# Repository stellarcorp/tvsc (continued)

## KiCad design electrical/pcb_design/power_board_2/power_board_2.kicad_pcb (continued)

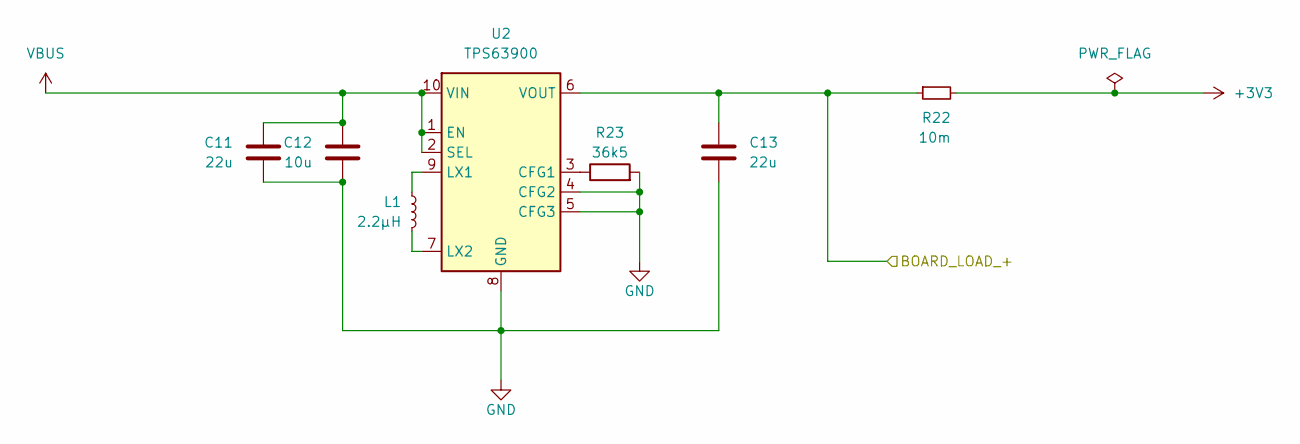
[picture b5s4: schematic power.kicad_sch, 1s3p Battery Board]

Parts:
C11, C13: 22u; Nondescript_C_0402_1005Metric
C12: 10u; Nondescript_C_0402_1005Metric
L1: 2.2µH; L_1008_2520Metric
R22: 10m; R_2512_6332Metric
R23: 36k5; Nondescript_R_0603_1608Metric
U2: TPS63900; WSON-10-1EP_2.5x2.5mm_P0.5mm_EP1.2x2mm_ThermalVias

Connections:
+3V3: R22.2; also elsewhere on the board
/Charger/BOARD_load+: C13.1, R22.1, U2.6 (VOUT); also elsewhere on the board
GND: C11.2, C12.2, C13.2, R23.2, U2.4 (CFG2), U2.5 (CFG3), U2.8 (GND), U2.11 (GND); also elsewhere on the board
unnamed: R23.1, U2.3 (CFG1)
unnamed: L1.2, U2.9 (LX1)
unnamed: L1.1, U2.7 (LX2)
VBUS: C11.1, C12.1, U2.1 (EN), U2.2 (SEL), U2.10 (VIN); also elsewhere on the board

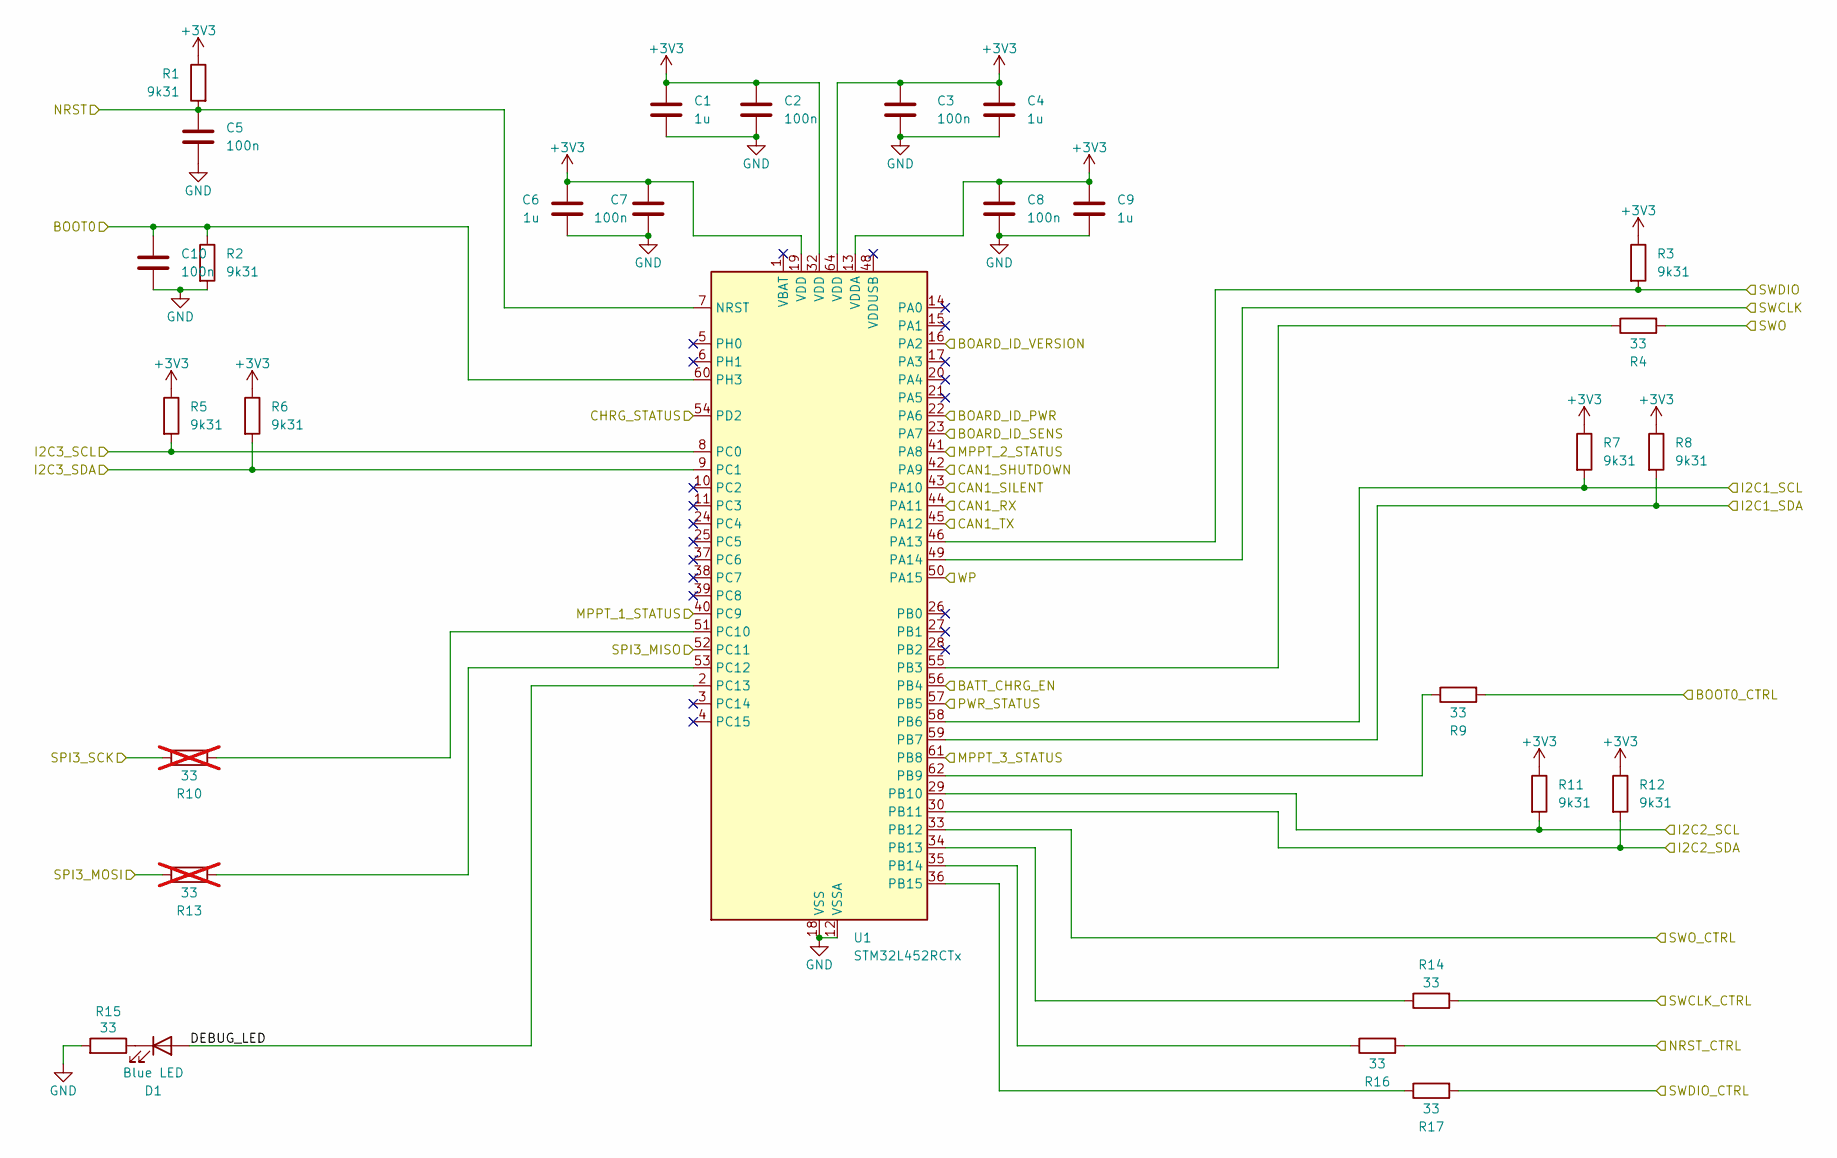
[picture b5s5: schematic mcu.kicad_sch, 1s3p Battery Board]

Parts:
C1, C4, C6, C9: 1u; Nondescript_C_0402_1005Metric
C2, C3, C5, C7, C8, C10: 100n; Nondescript_C_0402_1005Metric
D1: Blue LED; LED_0603_1608Metric
R1, R2, R3, R5, R6, R7, R8, R11, R12: 9k31; Nondescript_R_0402_1005Metric
R4, R9, R14, R15, R16, R17: 33; Nondescript_R_0402_1005Metric
R10: 33; Nondescript_R_0402_1005Metric; not fitted
R13: 33; not fitted
U1: STM32L452RCTx; LQFP-64_10x10mm_P0.5mm

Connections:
+3V3: C1.1, C2.1, C3.1, C4.1, C6.1, C7.1, C8.1, C9.1, R1.1, R3.1, R5.1, R6.1, R7.1, R8.1, R11.1, R12.1, U1.13 (VDDA), U1.19 (VDD), U1.32 (VDD), U1.64 (VDD); also elsewhere on the board
/BOOT0: C10.1, R2.1, U1.60 (PH3); also elsewhere on the board
/Board Identification/BOARD_ID_POWER: U1.22 (PA6); also elsewhere on the board
/Board Identification/BOARD_ID_SENSE: U1.23 (PA7); also elsewhere on the board
/CAN bus/CAN_RX: U1.44 (PA11); also elsewhere on the board
/CAN bus/CAN_SHUTDOWN: U1.42 (PA9); also elsewhere on the board
/CAN bus/CAN_SILENT: U1.43 (PA10); also elsewhere on the board
/CAN bus/CAN_TX: U1.45 (PA12); also elsewhere on the board
/CTRL.BOOT0: R9.2; also elsewhere on the board
/CTRL.NRST: R16.2; also elsewhere on the board
/CTRL.SWCLK: R14.2; also elsewhere on the board
/CTRL.SWDIO: R17.2; also elsewhere on the board
/CTRL.SWO: U1.33 (PB12); also elsewhere on the board
/Charger/BATT_CHRG_EN: U1.56 (PB4); also elsewhere on the board
/Charger/CHRG_STATUS: U1.54 (PD2); also elsewhere on the board
/Charger/I2C1_SDA: R8.2, U1.59 (PB7); also elsewhere on the board
/Charger/I2C1_SLC: R7.2, U1.58 (PB6); also elsewhere on the board
/Charger/I2C2_SDA: R12.2, U1.30 (PB11); also elsewhere on the board
/Charger/I2C2_SLC: R11.2, U1.29 (PB10); also elsewhere on the board
/Charger/I2C3_SDA: R6.2, U1.9 (PC1); also elsewhere on the board
/Charger/I2C3_SLC: R5.2, U1.8 (PC0); also elsewhere on the board
/Charger/MPPT_1_STATUS: U1.40 (PC9); also elsewhere on the board
/Charger/MPPT_2_STATUS: U1.41 (PA8); also elsewhere on the board
/Charger/MPPT_3_STATUS: U1.61 (PB8); also elsewhere on the board
/Charger/PWR_STATUS: U1.57 (PB5); also elsewhere on the board
/Charger/WP: U1.50 (PA15); also elsewhere on the board
/MCU/DEBUG_LED: D1.2 (A), U1.2 (PC13)
/MCU/SPI3_MISO: U1.52 (PC11)
/NRST: C5.1, R1.2, U1.7 (NRST); also elsewhere on the board
/SWCLK: U1.49 (PA14); also elsewhere on the board
/SWDIO: R3.2, U1.46 (PA13); also elsewhere on the board
/SWO: R4.2; also elsewhere on the board
GND: C1.2, C2.2, C3.2, C4.2, C5.2, C6.2, C7.2, C8.2, C9.2, C10.2, R2.2, R15.2, U1.12 (VSSA), U1.16 (PA2), U1.18 (VSS), U1.31 (VSS), U1.47 (VSS), U1.63 (VSS); also elsewhere on the board
unnamed: D1.1 (K), R15.1
unnamed: R4.1, U1.55 (PB3)
unnamed: R9.1, U1.62 (PB9)
unnamed: R14.1, U1.34 (PB13)
unnamed: R16.1, U1.35 (PB14)
unnamed: R17.1, U1.36 (PB15)
unnamed: R10.2, U1.51 (PC10)
unnamed: R13.2, U1.53 (PC12)

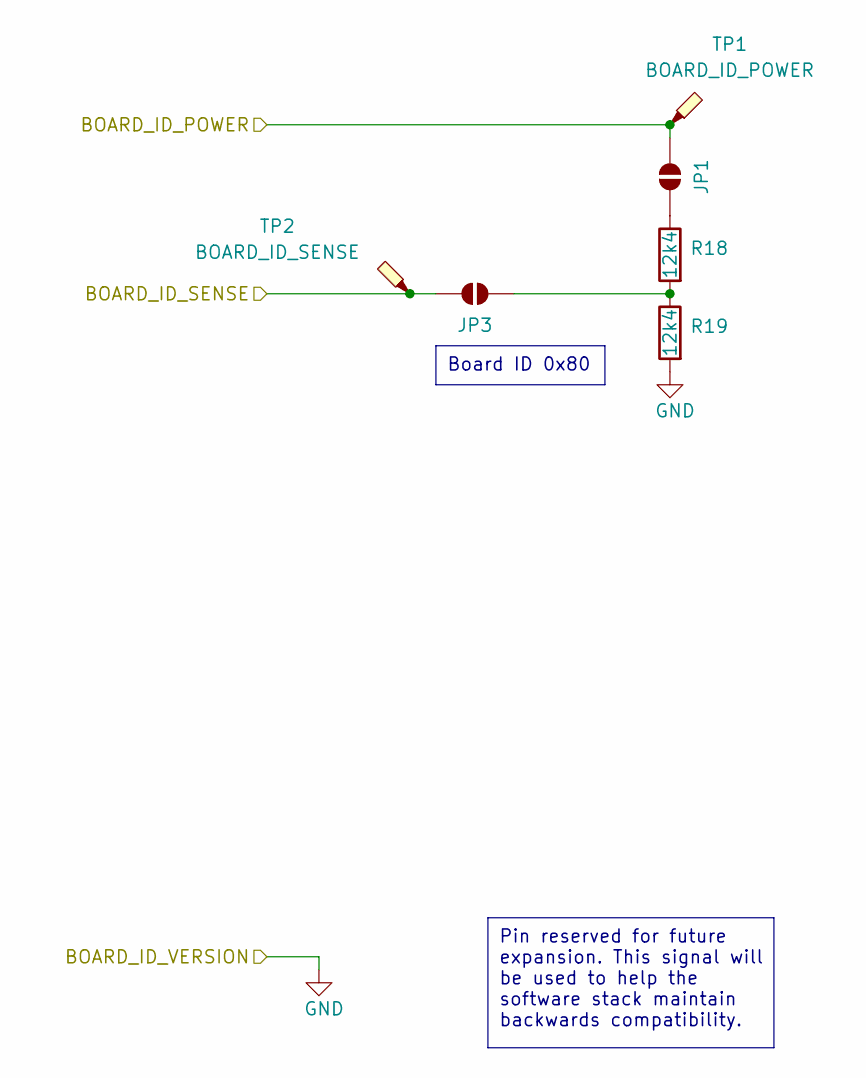
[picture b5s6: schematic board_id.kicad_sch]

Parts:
JP1, JP3: SolderJumper_2_Open; SolderJumper-2_P1.3mm_Open_RoundedPad1.0x1.5mm
R18, R19: 12k4; Nondescript_R_0402_1005Metric
TP1: BOARD_ID_POWER; TestPoint_Pad_D1.5mm
TP2: BOARD_ID_SENSE; TestPoint_Pad_D1.5mm

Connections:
/Board Identification/BOARD_ID_POWER: JP1.2 (B), TP1.1; also elsewhere on the board
/Board Identification/BOARD_ID_SENSE: JP3.1 (A), TP2.1; also elsewhere on the board
GND: R19.2; also elsewhere on the board
unnamed: JP1.1 (A), R18.1
unnamed: JP3.2 (B), R18.2, R19.1

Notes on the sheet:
Pin reserved for future expansion. This signal will be used to help the software stack maintain backwards compatibility.
Board ID 0x80

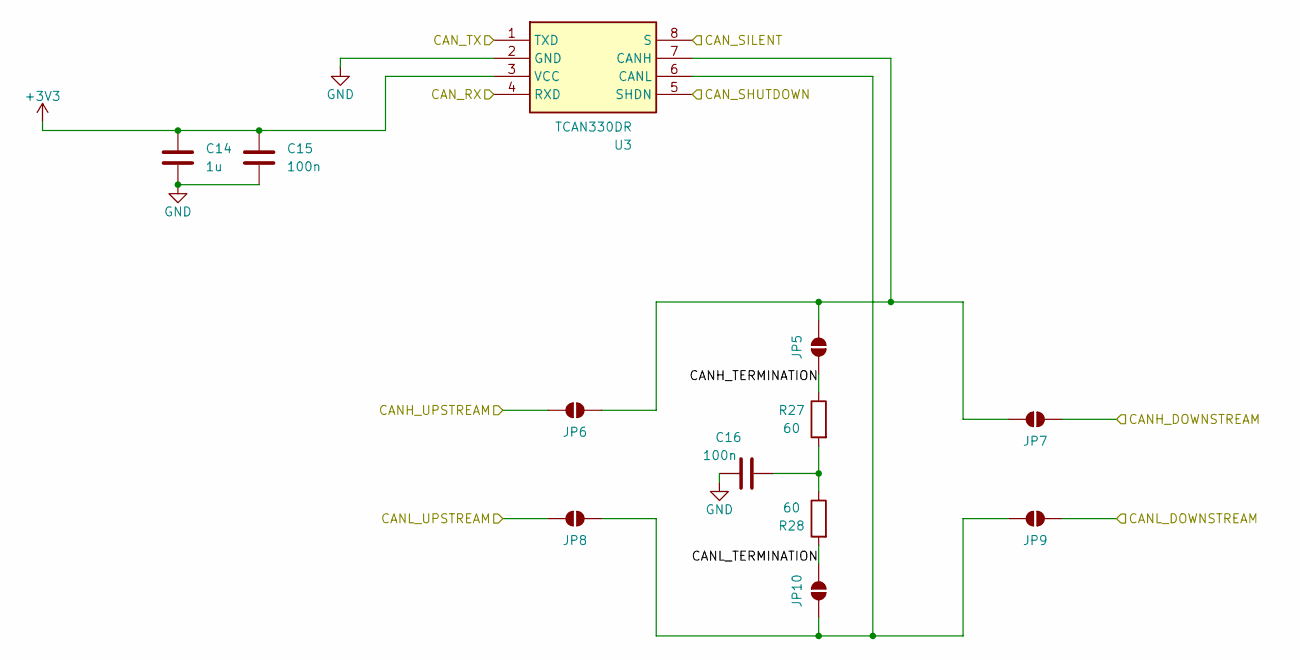
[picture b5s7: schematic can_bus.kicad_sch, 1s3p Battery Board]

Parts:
C14: 1u; Nondescript_C_0402_1005Metric
C15, C16: 100n; Nondescript_C_0402_1005Metric
JP5, JP6, JP7, JP8, JP9, JP10: SolderJumper_2_Open; SolderJumper-2_P1.3mm_Open_RoundedPad1.0x1.5mm
R27, R28: 60; Nondescript_R_0402_1005Metric
U3: TCAN330DR; SOIC127P600X175-8N; Manufacturer Part Number TCAN330DR

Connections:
+3V3: C14.1, C15.1, U3.3 (VCC); also elsewhere on the board
/CAN bus/CANH_TERMINATION: JP5.2 (B), R27.1
/CAN bus/CANL_TERMINATION: JP10.1 (A), R28.2
/CAN bus/CAN_RX: U3.4 (RXD); also elsewhere on the board
/CAN bus/CAN_SHUTDOWN: U3.5 (SHDN); also elsewhere on the board
/CAN bus/CAN_SILENT: U3.8 (S); also elsewhere on the board
/CAN bus/CAN_TX: U3.1 (TXD); also elsewhere on the board
/CANH_DOWNSTREAM: JP7.2 (B); also elsewhere on the board
/CANH_UPSTREAM: JP6.1 (A); also elsewhere on the board
/CANL_DOWNSTREAM: JP9.2 (B); also elsewhere on the board
/CANL_UPSTREAM: JP8.1 (A); also elsewhere on the board
GND: C14.2, C15.2, C16.1, U3.2 (GND); also elsewhere on the board
unnamed: C16.2, R27.2, R28.1
unnamed: JP5.1 (A), JP6.2 (B), JP7.1 (A), U3.7 (CANH)
unnamed: JP8.2 (B), JP9.1 (A), JP10.2 (B), U3.6 (CANL)

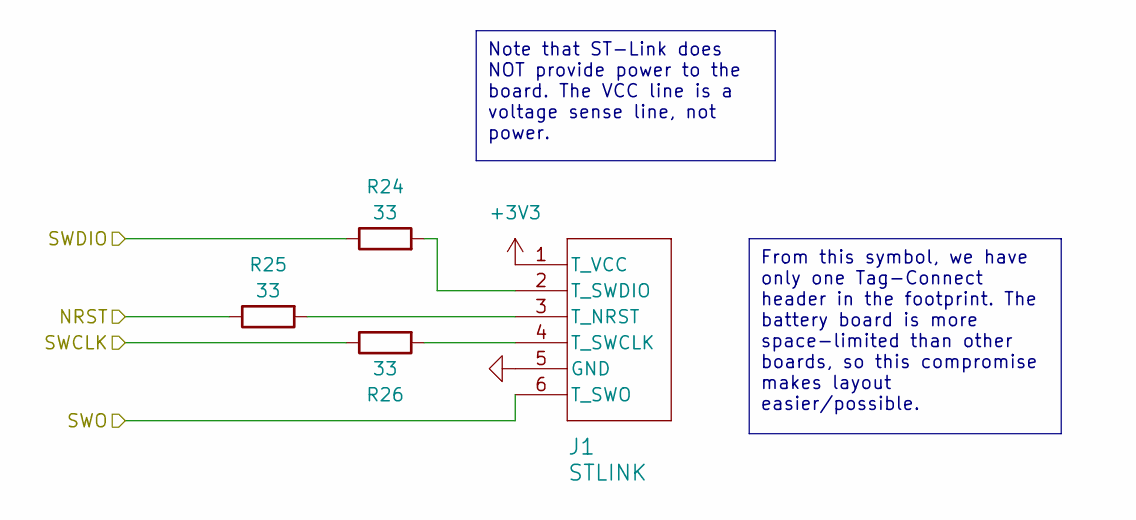
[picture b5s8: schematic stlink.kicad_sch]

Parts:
J1: STLINK; Tag-Connect_TC2030-IDC-NL_2x03_P1.27mm_Vertical
R24, R25, R26: 33; Nondescript_R_0402_1005Metric

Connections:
+3V3: J1.1 (T_VCC); also elsewhere on the board
/NRST: R25.1; also elsewhere on the board
/SWCLK: R26.1; also elsewhere on the board
/SWDIO: R24.1; also elsewhere on the board
/SWO: J1.6 (T_SWO); also elsewhere on the board
GND: J1.5 (GND); also elsewhere on the board
unnamed: J1.3 (T_NRST), R25.2
unnamed: J1.4 (T_SWCLK), R26.2
unnamed: J1.2 (T_SWDIO), R24.2

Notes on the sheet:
Note that ST-Link does NOT provide power to the board. The VCC line is a voltage sense line, not power.
From this symbol, we have only one Tag-Connect header in the footprint. The battery board is more space-limited than other boards, so this compromise makes layout easier/possible.

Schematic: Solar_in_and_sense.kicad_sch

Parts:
D2, D3, D4, D5, D6, D7, D8, D9, D10: SM74611KTTR; SM74611; PARTREV B
J5, J6: Molex_504050-0691; Manufacturer Part Number 504050-0691
R20, R21, R43, R44, R45, R46: 1; R_2512_6332Metric
R49, R50: 9k31; Nondescript_R_0402_1005Metric
U12, U13: PAC1932T-I/JQ; PAC1934

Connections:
+3V3: R49.1, R50.1, U12.2 (VDD), U12.15 (VDDI/O), U12.16 (*PWRDN), U13.2 (VDD), U13.9 (SENSE4-), U13.15 (VDDI/O), U13.16 (*PWRDN); also elsewhere on the board
/Charger/BOARD_load+: U13.10 (SENSE4+); also elsewhere on the board
/Charger/BUS_Load+: U13.11 (SENSE1+); also elsewhere on the board
/Charger/I2C2_SDA: U13.4 (SM_CLK); also elsewhere on the board
/Charger/I2C2_SLC: U13.5 (SM_DATA); also elsewhere on the board
/Charger/I2C3_SDA: U12.4 (SM_CLK); also elsewhere on the board
/Charger/I2C3_SLC: U12.5 (SM_DATA); also elsewhere on the board
/Charger/Solar and Sense/MPPT_1/VOUT: D4.1 (ANODE_1), D4.3 (ANODE_3); also elsewhere on the board
/Charger/Solar and Sense/MPPT_2/VOUT: D7.1 (ANODE_1), D7.3 (ANODE_3); also elsewhere on the board
/Charger/Solar and Sense/MPPT_3/VOUT: D10.1 (ANODE_1), D10.3 (ANODE_3); also elsewhere on the board
/Charger/Solar and Sense/MPPT_OUT: D4.4 (CATHODE), D7.4 (CATHODE), D10.4 (CATHODE); also elsewhere on the board
/Charger/Solar and Sense/SSx1: R21.2, U13.7 (SENSE3-); also elsewhere on the board
/Charger/Solar and Sense/SSx2: D3.1 (ANODE_1), D3.3 (ANODE_3), R20.1, U13.14 (SENSE2-)
/Charger/Solar and Sense/SSy1: R44.2, U12.12 (SENSE1-); also elsewhere on the board
/Charger/Solar and Sense/SSy2: D6.1 (ANODE_1), D6.3 (ANODE_3), R43.1, U12.14 (SENSE2-)
/Charger/Solar and Sense/SSz1: R46.2, U12.7 (SENSE3-); also elsewhere on the board
/Charger/Solar and Sense/SSz2: D9.1 (ANODE_1), D9.3 (ANODE_3), R45.1, U12.9 (SENSE4-)
/Charger/Solar and Sense/Solar_x1+: D3.4 (CATHODE), J5.1, R21.1, U13.8 (SENSE3+)
/Charger/Solar and Sense/Solar_x2+: D2.4 (CATHODE), J5.2, J6.1, R20.2, U13.13 (SENSE2+)
/Charger/Solar and Sense/Solar_y1+: D6.4 (CATHODE), J5.3, R44.1, U12.11 (SENSE1+)
/Charger/Solar and Sense/Solar_y2+: D5.4 (CATHODE), J5.4, J6.3, R43.2, U12.13 (SENSE2+)
/Charger/Solar and Sense/Solar_z1+: D9.4 (CATHODE), J5.5, R46.1, U12.8 (SENSE3+)
/Charger/Solar and Sense/Solar_z2+: D8.4 (CATHODE), J5.6, J6.5, R45.2, U12.10 (SENSE4+)
GND: D2.1 (ANODE_1), D2.3 (ANODE_3), D5.1 (ANODE_1), D5.3 (ANODE_3), D8.1 (ANODE_1), D8.3 (ANODE_3), J5.7 (MP1), J5.8 (MP2), J6.2, J6.4, J6.6, J6.7 (MP1), J6.8 (MP2), U12.3 (GND), U12.6 (ADDRSEL), U13.3 (GND), U13.6 (ADDRSEL); also elsewhere on the board
unnamed: R49.2, U12.1 (SLOW/*ALERT)
unnamed: R50.2, U13.1 (SLOW/*ALERT)
VBUS: U13.12 (SENSE1-); also elsewhere on the board

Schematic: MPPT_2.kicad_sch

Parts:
C26, C27: 22n; Nondescript_C_0402_1005Metric
C28: 47u; Nondescript_C_0402_1005Metric
C29: 1u; Nondescript_C_0402_1005Metric
C30: 4.7u; Nondescript_C_0402_1005Metric
C31: 10p; Nondescript_C_0402_1005Metric
L3: 6.8u; LQH44PN_PR_MUR
R35: 4M; Nondescript_R_0402_1005Metric
R36: 200k; Nondescript_R_0402_1005Metric
R37: 100k; Nondescript_R_0402_1005Metric
R38: 1M; Nondescript_R_0402_1005Metric
U8: LTC3130EUDC-PBF; LTC3130
U9: AD5242BRUZ1M; AD5242

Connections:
+3V3: U9.5 (VDD), U9.6 (SHDN*); also elsewhere on the board
/Charger/I2C1_SDA: U9.8 (SDA); also elsewhere on the board
/Charger/I2C1_SLC: U9.7 (SCL); also elsewhere on the board
/Charger/MPPT_2_STATUS: U8.13 (PGOOD); also elsewhere on the board
/Charger/Solar and Sense/MPPT_2/CHRG_CTRL_2: R35.2, R36.2, R38.1, U8.9 (VS2/FB)
/Charger/Solar and Sense/MPPT_2/MPPT_2_DP_W: R37.1, U8.6 (MPPC), U9.3 (W1)
/Charger/Solar and Sense/MPPT_2/VOUT: C31.1, R35.1, U8.12 (EXTVCC), U8.14 (VOUT); also elsewhere on the board
/Charger/Solar and Sense/SSy1: C28.1, C29.1, U8.2 (PVIN), U8.3 (VIN), U8.4 (RUN), U9.2 (A1); also elsewhere on the board
GND: C28.2, C29.2, C30.2, R37.2, R38.2, U8.7 (GND), U8.8 (GND), U8.11 (MODE), U8.18 (PGND), U8.19 (PGND), U9.4 (B1), U9.9 (AD0), U9.10 (AD1), U9.11 (DGND), U9.12 (VSS); also elsewhere on the board
unnamed: C31.2, R36.1
unnamed: C26.1, U8.1 (BST1)
unnamed: C27.1, U8.16 (BST2)
unnamed: C26.2, L3.1, U8.20 (SW1)
unnamed: C27.2, L3.2, U8.15 (SW2)
unnamed: C30.1, U8.5 (VCC), U8.10 (VS1/ILIM)

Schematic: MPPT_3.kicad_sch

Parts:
C32, C33: 22n; Nondescript_C_0402_1005Metric
C34: 47u; Nondescript_C_0402_1005Metric
C35: 1u; Nondescript_C_0402_1005Metric
C36: 4.7u; Nondescript_C_0402_1005Metric
C37: 10p; Nondescript_C_0402_1005Metric
L4: 6.8u; LQH44PN_PR_MUR
R39: 4M; Nondescript_R_0402_1005Metric
R40: 200k; Nondescript_R_0402_1005Metric
R41: 100k; Nondescript_R_0402_1005Metric
R42: 1M; Nondescript_R_0402_1005Metric
U10: LTC3130EUDC-PBF; LTC3130
U11: AD5242BRUZ1M; AD5242

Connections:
+3V3: U11.5 (VDD), U11.6 (SHDN*); also elsewhere on the board
/Charger/I2C3_SDA: U11.8 (SDA); also elsewhere on the board
/Charger/I2C3_SLC: U11.7 (SCL); also elsewhere on the board
/Charger/MPPT_3_STATUS: U10.13 (PGOOD); also elsewhere on the board
/Charger/Solar and Sense/MPPT_3/CHRG_CTRL_3: R39.2, R40.2, R42.1, U10.9 (VS2/FB)
/Charger/Solar and Sense/MPPT_3/MPPT_3_DP_W: R41.1, U10.6 (MPPC), U11.3 (W1)
/Charger/Solar and Sense/MPPT_3/VOUT: C37.1, R39.1, U10.12 (EXTVCC), U10.14 (VOUT); also elsewhere on the board
/Charger/Solar and Sense/SSz1: C34.1, C35.1, U10.2 (PVIN), U10.3 (VIN), U10.4 (RUN), U11.2 (A1); also elsewhere on the board
GND: C34.2, C35.2, C36.2, R41.2, R42.2, U10.7 (GND), U10.8 (GND), U10.11 (MODE), U10.18 (PGND), U10.19 (PGND), U11.4 (B1), U11.9 (AD0), U11.10 (AD1), U11.11 (DGND), U11.12 (VSS); also elsewhere on the board
unnamed: C37.2, R40.1
unnamed: C32.1, U10.1 (BST1)
unnamed: C33.1, U10.16 (BST2)
unnamed: C32.2, L4.1, U10.20 (SW1)
unnamed: C33.2, L4.2, U10.15 (SW2)
unnamed: C36.1, U10.5 (VCC), U10.10 (VS1/ILIM)

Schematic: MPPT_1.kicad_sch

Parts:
C20, C21: 22n; Nondescript_C_0402_1005Metric
C22: 47u; Nondescript_C_0402_1005Metric
C23: 1u; Nondescript_C_0402_1005Metric
C24: 4.7u; Nondescript_C_0402_1005Metric
C25: 10p; Nondescript_C_0402_1005Metric
L2: 6.8u; LQH44PN_PR_MUR
R31: 4M; Nondescript_R_0402_1005Metric
R32: 200k; Nondescript_R_0402_1005Metric
R33: 100k; Nondescript_R_0402_1005Metric
R34: 1M; Nondescript_R_0402_1005Metric
U6: LTC3130EUDC-PBF; LTC3130
U7: AD5242BRUZ1M; AD5242

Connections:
+3V3: U7.5 (VDD), U7.6 (SHDN*); also elsewhere on the board
/Charger/I2C2_SDA: U7.8 (SDA); also elsewhere on the board
/Charger/I2C2_SLC: U7.7 (SCL); also elsewhere on the board
/Charger/MPPT_1_STATUS: U6.13 (PGOOD); also elsewhere on the board
/Charger/Solar and Sense/MPPT_1/CHRG_CTRL_1: R31.2, R32.2, R34.1, U6.9 (VS2/FB)
/Charger/Solar and Sense/MPPT_1/MPPT_1_DP_W: R33.1, U6.6 (MPPC), U7.3 (W1)
/Charger/Solar and Sense/MPPT_1/VOUT: C25.1, R31.1, U6.12 (EXTVCC), U6.14 (VOUT); also elsewhere on the board
/Charger/Solar and Sense/SSx1: C22.1, C23.1, U6.2 (PVIN), U6.3 (VIN), U6.4 (RUN), U7.2 (A1); also elsewhere on the board
GND: C22.2, C23.2, C24.2, R33.2, R34.2, U6.7 (GND), U6.8 (GND), U6.11 (MODE), U6.18 (PGND), U6.19 (PGND), U7.4 (B1), U7.9 (AD0), U7.10 (AD1), U7.11 (DGND), U7.12 (VSS); also elsewhere on the board
unnamed: C25.2, R32.1
unnamed: C20.1, U6.1 (BST1)
unnamed: C21.1, U6.16 (BST2)
unnamed: C20.2, L2.1, U6.20 (SW1)
unnamed: C21.2, L2.2, U6.15 (SW2)
unnamed: C24.1, U6.5 (VCC), U6.10 (VS1/ILIM)

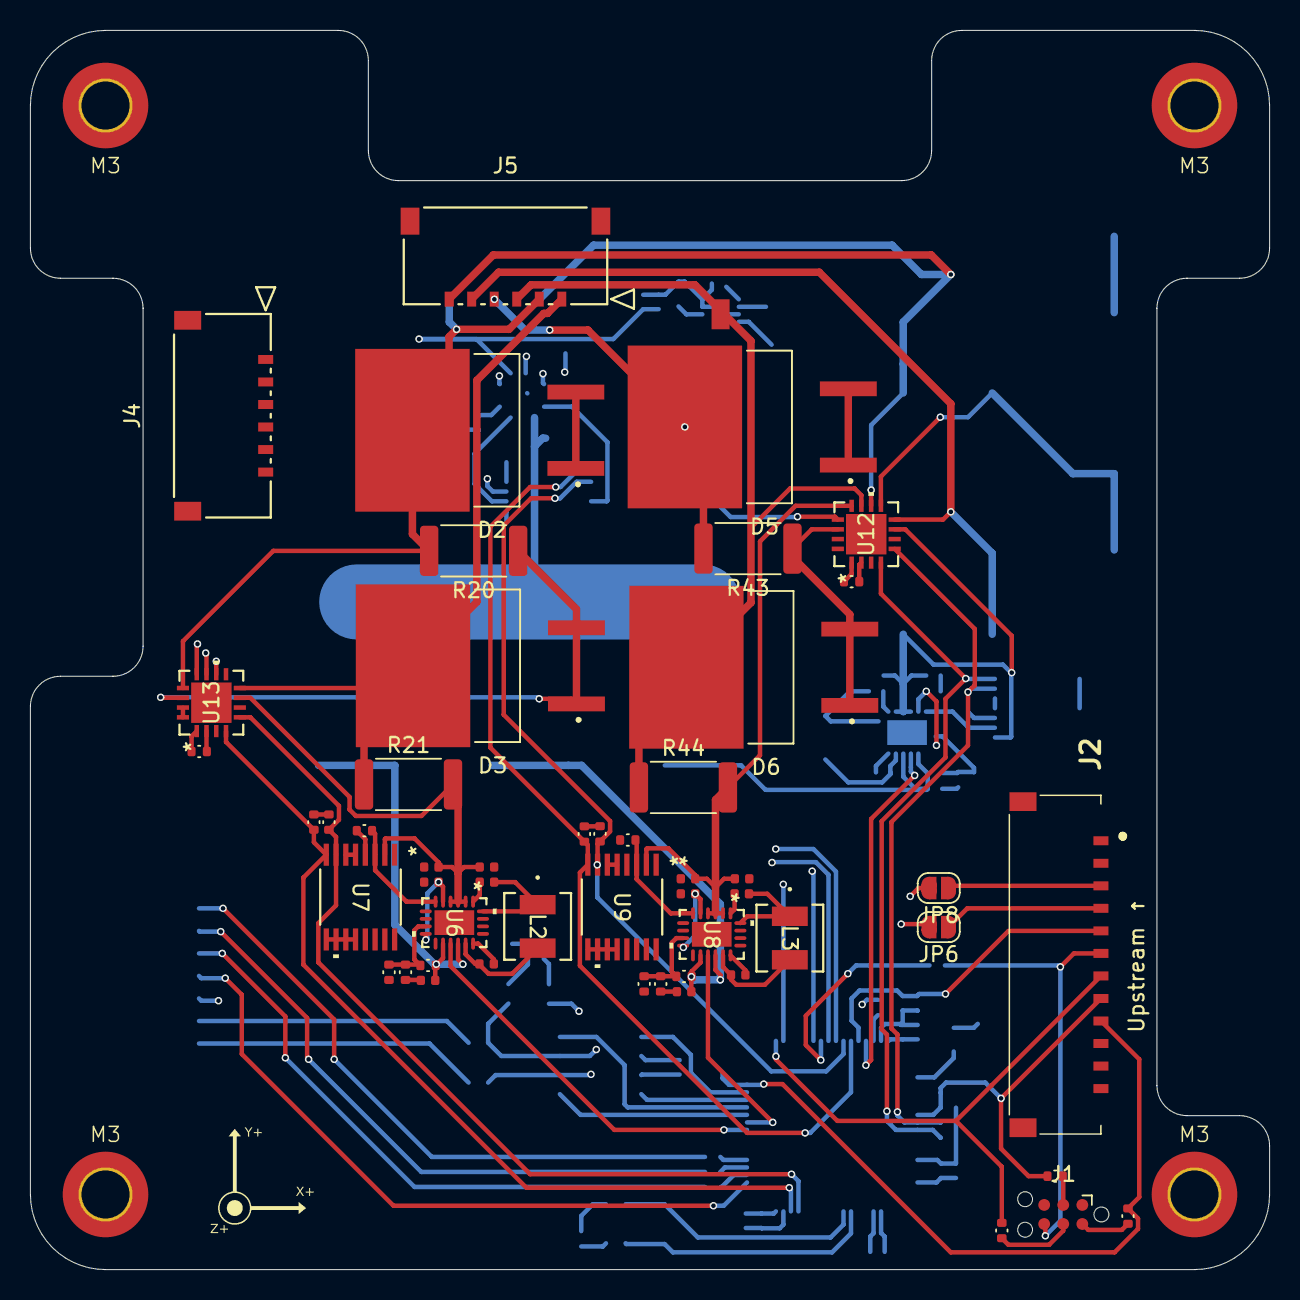
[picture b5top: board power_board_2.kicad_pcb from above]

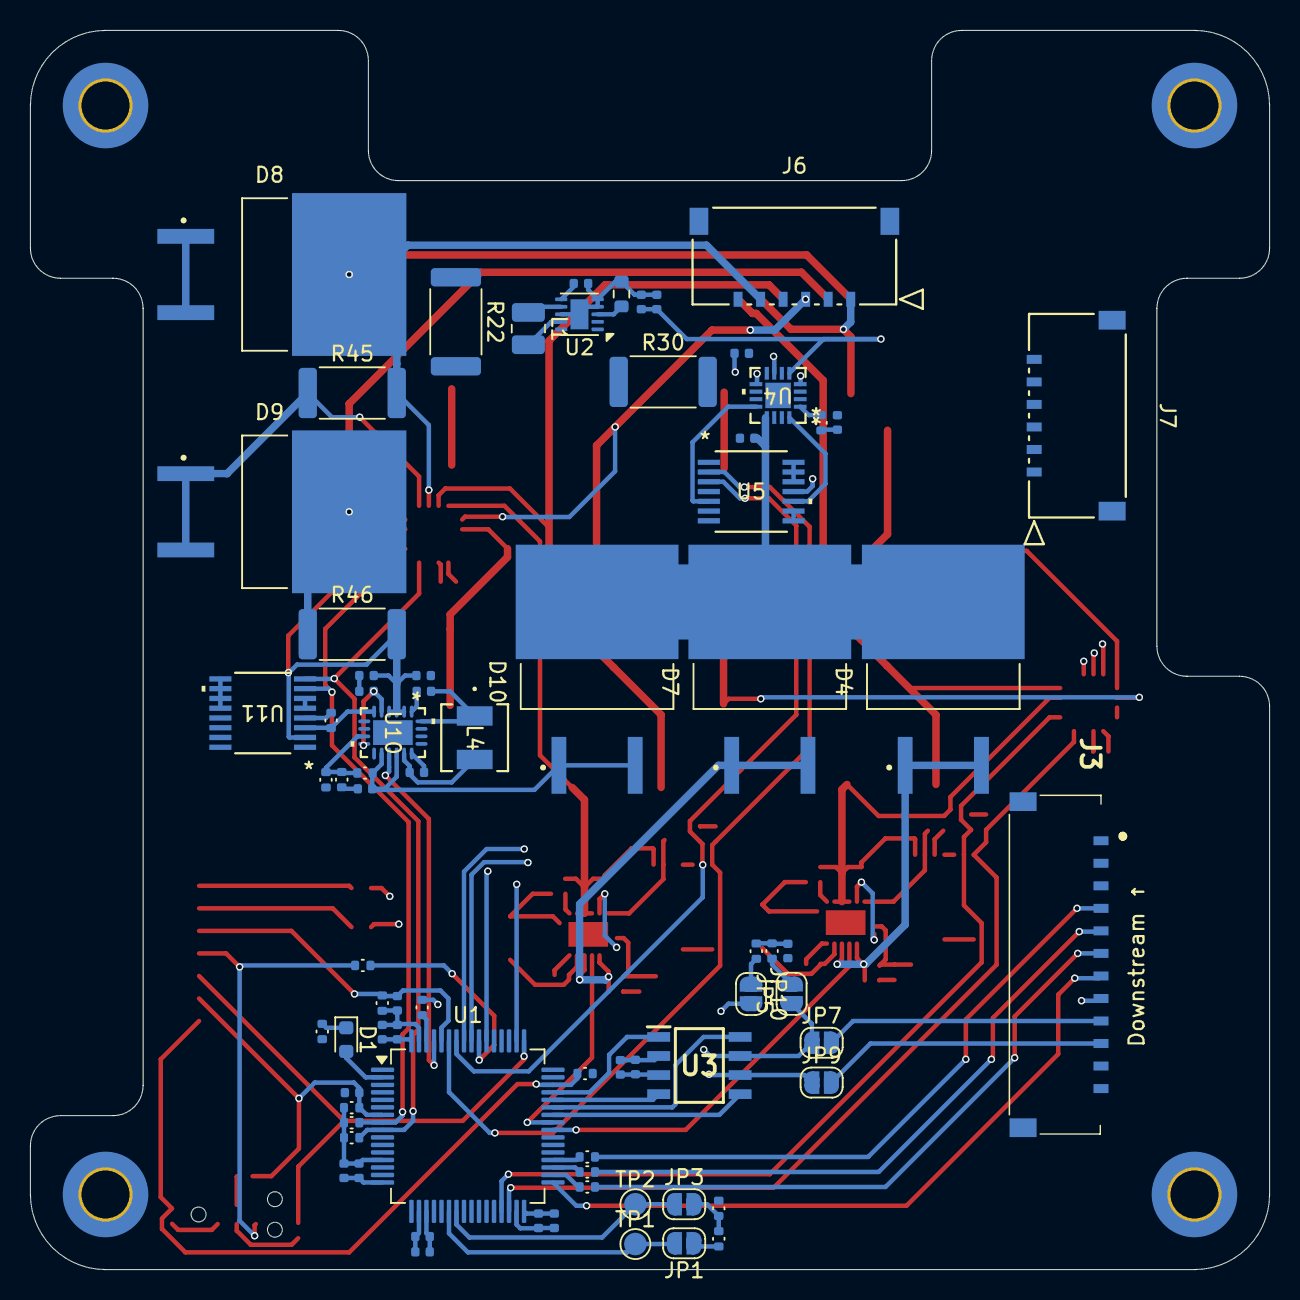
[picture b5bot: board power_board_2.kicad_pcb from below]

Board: 4 copper layers, 82.5 x 82.5 mm, 128 parts (76 on the bottom side), 104 nets.

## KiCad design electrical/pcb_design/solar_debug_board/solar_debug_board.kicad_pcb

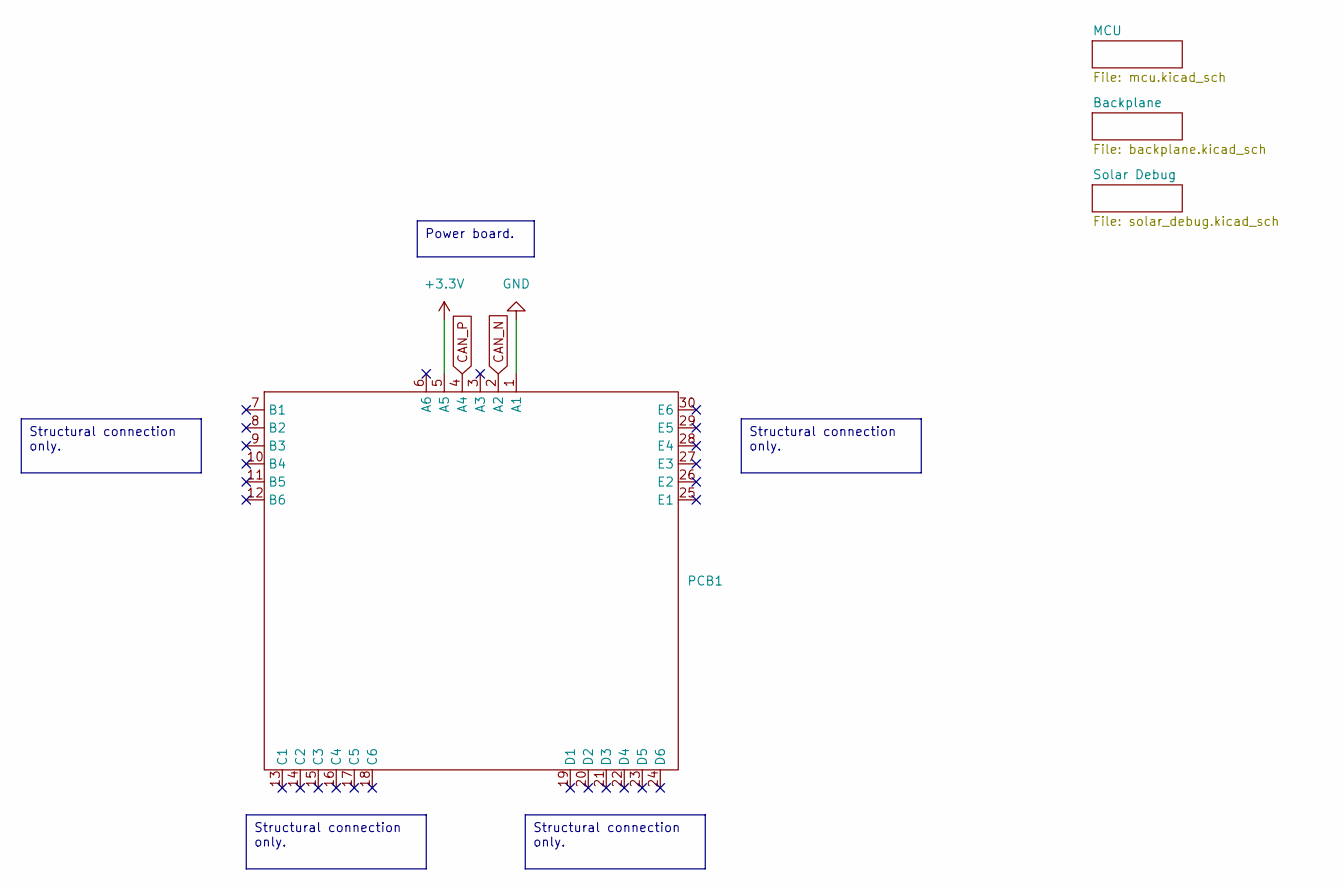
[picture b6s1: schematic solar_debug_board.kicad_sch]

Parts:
PCB1: Core_Board_PCB_Shape

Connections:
+3.3V: PCB1.5 (A5); also elsewhere on the board
CAN_N: PCB1.2 (A2); also elsewhere on the board
CAN_P: PCB1.4 (A4); also elsewhere on the board
GND: PCB1.1 (A1); also elsewhere on the board

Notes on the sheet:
Structural connection only.
Power board.

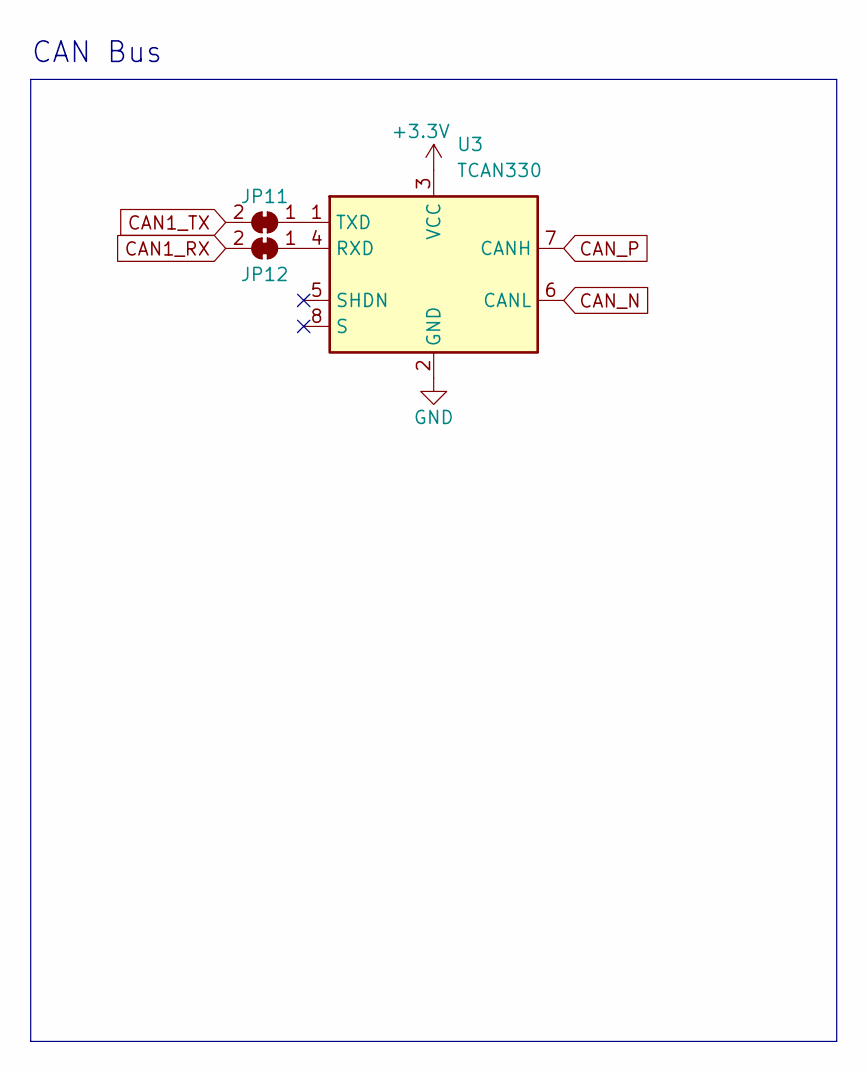
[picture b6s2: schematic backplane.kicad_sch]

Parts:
JP11, JP12: SolderJumper_2_Bridged; SolderJumper-2_P1.3mm_Bridged_RoundedPad1.0x1.5mm
U3: TCAN330; SOT-23-8; Manufacturer Part Number TCAN330DCNR

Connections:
+3.3V: U3.3 (VCC); also elsewhere on the board
CAN1_RX: JP12.2 (B); also elsewhere on the board
CAN1_TX: JP11.2 (B); also elsewhere on the board
CAN_N: U3.6 (CANL); also elsewhere on the board
CAN_P: U3.7 (CANH); also elsewhere on the board
GND: U3.2 (GND); also elsewhere on the board
unnamed: JP11.1 (A), U3.1 (TXD)
unnamed: JP12.1 (A), U3.4 (RXD)

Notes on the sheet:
CAN Bus

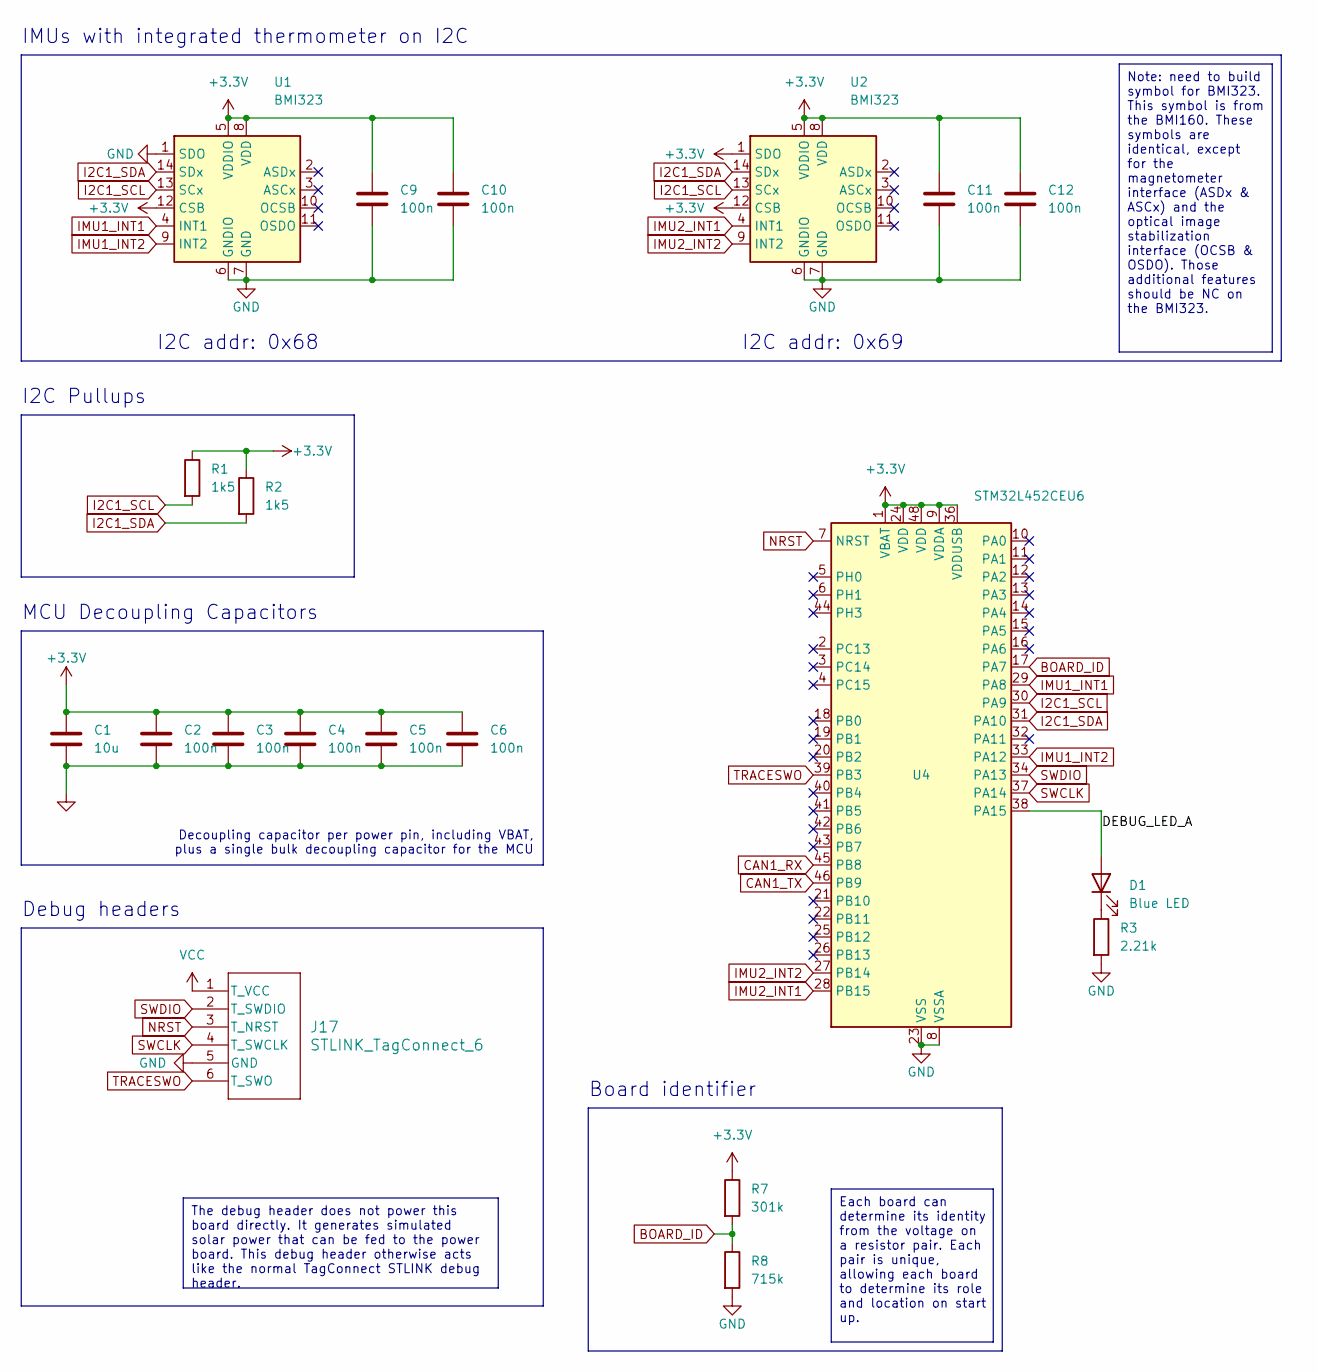
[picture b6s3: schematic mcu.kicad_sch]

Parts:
C1: 10u; C_0603_1608Metric; MPN C344022
C2, C3, C4, C5, C6: 100n; Nondescript_C_0402_1005Metric; MPN C2649549
C9, C10, C11, C12: 100n; Nondescript_C_0402_1005Metric; Manufacturer Part Number GCM155R71H104KE02J
D1: Blue LED; LED_0603_1608Metric; MPN C72041
J17: STLINK_TagConnect_6; Tag-Connect_TC2030-IDC-NL_2x03_P1.27mm_Vertical
R1, R2: 1k5; R_0402_1005Metric; MPN C25867
R3: 2.21k; Nondescript_R_0402_1005Metric; MPN C305298
R7: 301k; Nondescript_R_0402_1005Metric; MPN C25775
R8: 715k; Nondescript_R_0402_1005Metric; MPN C270585
U1, U2: BMI323; Bosch_LGA-14_3x2.5mm_P0.5mm; MPN C5368700
U4: STM32L452CEU6; QFN-48-1EP_7x7mm_P0.5mm_EP5.6x5.6mm_ThermalVias; MPN C222355

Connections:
+3.3V: C1.1, C2.1, C3.1, C4.1, C5.1, C6.1, C9.1, C10.1, C11.1, C12.1, R1.1, R2.1, R7.1, U1.5 (VDDIO), U1.8 (VDD), U1.12 (CSB), U2.1 (SDO), U2.5 (VDDIO), U2.8 (VDD), U2.12 (CSB), U4.1 (VBAT), U4.9 (VDDA), U4.24 (VDD), U4.36 (VDDUSB), U4.48 (VDD); also elsewhere on the board
/MCU/DEBUG_LED_A: D1.2 (A), U4.38 (PA15)
BOARD_ID: R7.2, R8.1, U4.17 (PA7)
CAN1_RX: U4.45 (PB8); also elsewhere on the board
CAN1_TX: U4.46 (PB9); also elsewhere on the board
GND: C1.2, C2.2, C3.2, C4.2, C5.2, C6.2, C9.2, C10.2, C11.2, C12.2, J17.5 (GND), R3.2, R8.2, U1.1 (SDO), U1.6 (GNDIO), U1.7 (GND), U2.6 (GNDIO), U2.7 (GND), U4.8 (VSSA), U4.23 (VSS), U4.35 (VSS), U4.47 (VSS), U4.49 (VSS); also elsewhere on the board
I2C1_SCL: R1.2, U1.13 (SCx), U2.13 (SCx), U4.30 (PA9)
I2C1_SDA: R2.2, U1.14 (SDx), U2.14 (SDx), U4.31 (PA10)
IMU1_INT1: U1.4 (INT1), U4.29 (PA8)
IMU1_INT2: U1.9 (INT2), U4.33 (PA12)
IMU2_INT1: U2.4 (INT1), U4.28 (PB15)
IMU2_INT2: U2.9 (INT2), U4.27 (PB14)
NRST: J17.3 (T_NRST), U4.7 (NRST)
unnamed: D1.1 (K), R3.1
SWCLK: J17.4 (T_SWCLK), U4.37 (PA14)
SWDIO: J17.2 (T_SWDIO), U4.34 (PA13)
TRACESWO: J17.6 (T_SWO), U4.39 (PB3)
VCC: J17.1 (T_VCC); also elsewhere on the board

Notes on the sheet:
The debug header does not power this board directly. It generates simulated solar power that can be fed to the power board. This debug header otherwise acts like the normal TagConnect STLINK debug header.
Each board can determine its identity from the voltage on a resistor pair. Each pair is unique, allowing each board to determine its role and location on start up.
Note: need to build symbol for BMI323. This symbol is from the BMI160. These symbols are identical, except for the magnetometer interface (ASDx & ASCx) and the optical image stabilization interface (OCSB & OSDO). Those additional features should be NC on the BMI323.
Debug headers
MCU Decoupling Capacitors
Decoupling capacitor per power pin, including VBAT, plus a single bulk decoupling capacitor for the MCU
Board identifier
I2C addr: 0x68
IMUs with integrated thermometer on I2C
I2C Pullups
I2C addr: 0x69
